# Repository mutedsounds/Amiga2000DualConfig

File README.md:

# Amiga2000DualConfig
Amiga 2000 Coprocessor Board to support 2 selectable CPUs, 2 selectable kickstart ROMs (+ 2x A/B configuration options) at boot or reset.

The **DualConfig** project was born out of an observation: some programs, games or demos don't work with all 680x0 processor models or all kickstart versions.

This project allows you to run the Amiga 2000 in legacy mode (68000 & Kickstart1.3) or with the legacy CPU and a more recent kickstart (68000 & Kickstart 3.x) or with a TerribleFire-type card (68030 & Kickstart3.x) for instance. It also provides two additional controls, one can be used to control a DF0 selector for instance. 

There is no need to power-off the Amiga to change the configuration. It can be changed anytime while the Amiga is powered-on. It will be taken in account on the next reset. Each of the 4 configuration parameters (CPU, Kickstart, param3, param4) can be selected using a latched SPST Off-On switch, with optional illumination.

The solution consists of two PCBs:

1. A "DualCpuAdapter" card that fits into the coprocessor slot. It is inspired by the [Open Amiga 2000 Copro Adapter](https://github.com/SukkoPera/OpenAmiga2000CoproAdapter) project. It allows:

   a) permanent installation of two CPUs in the Amiga with selection of one of the two installed CPUs via a SPST latched Off-On switch;

   b) selection of one of two Kickstarts via a SPST latch Off-On switch;

   c) optionally two other configuration parameters, each controlled via a latchsed SPST Off-On switch, one can be used to drive a ["DF0 Selector" board with a SPST control interface such as the one developped by Jussi Kilpelainen](https://jussikilpelainen.kapsi.fi/wordpress/?p=256)

   d) a led illumination driver for each parameter, enabling the use of illuminated switches 

2. A "DualKickAdapter" card that fits in the Kickstart DIP40 slot, allowing a permanent installation of two kickstart ROMs in the Amiga. Kickstart selection can be controlled either by the "DualCpuAdapter" card or by a DPDT On-On switch. 

The "DualKickAdapter" can be controlled by the "DualCpuAdapter" board by connecting 2 wires from the KICK1_CSn & KICK2_CSn header pins of the "DualCpuAdapter" board to the middle pins of the 2x3 header "SW DPDT", CSn_A & CSn_B.

The [CIT Relay GH Series](http://citrelay.com/view_switch.php?series=GH) are illuminated SPST latching off-on pushbutton switches with a small enough diameter of 10mm to be installed on the lower area of the bottom chassis of the Amiga 2000.

I made this project initially for personal use. It is operational and free of license. 

|:warning:**IMPORTANT: The KiCad files provided in the github repository have been translated from another commercial PCB design tool. The latest beta version (7.99) is required to open the files. I strongly advise to double check the KiCad PCB design files before sending to production. Please feel free to propose document updates.** |
|-----------------------------------------|

DualCpuAdapter, CPU1 side  | DualCpuAdapter, CPU2 side | DualKickAdapter
:-------------------------:|:-------------------------:|:-------------------------:
|  |  |  |

:camera:
|-----------------------------------------|

Legacy configuration 68000 (switch off) with Kickstart 1.3 (switch off) | Legacy CPU 68000 (switch off) with Kickstart 3.2.2 (switch on) | TF536 accelerator (switch on) with Kickstart 3.2.2 (switch on)
:-------------------------:|:-------------------------:|:-------------------------:
|  |  |  |

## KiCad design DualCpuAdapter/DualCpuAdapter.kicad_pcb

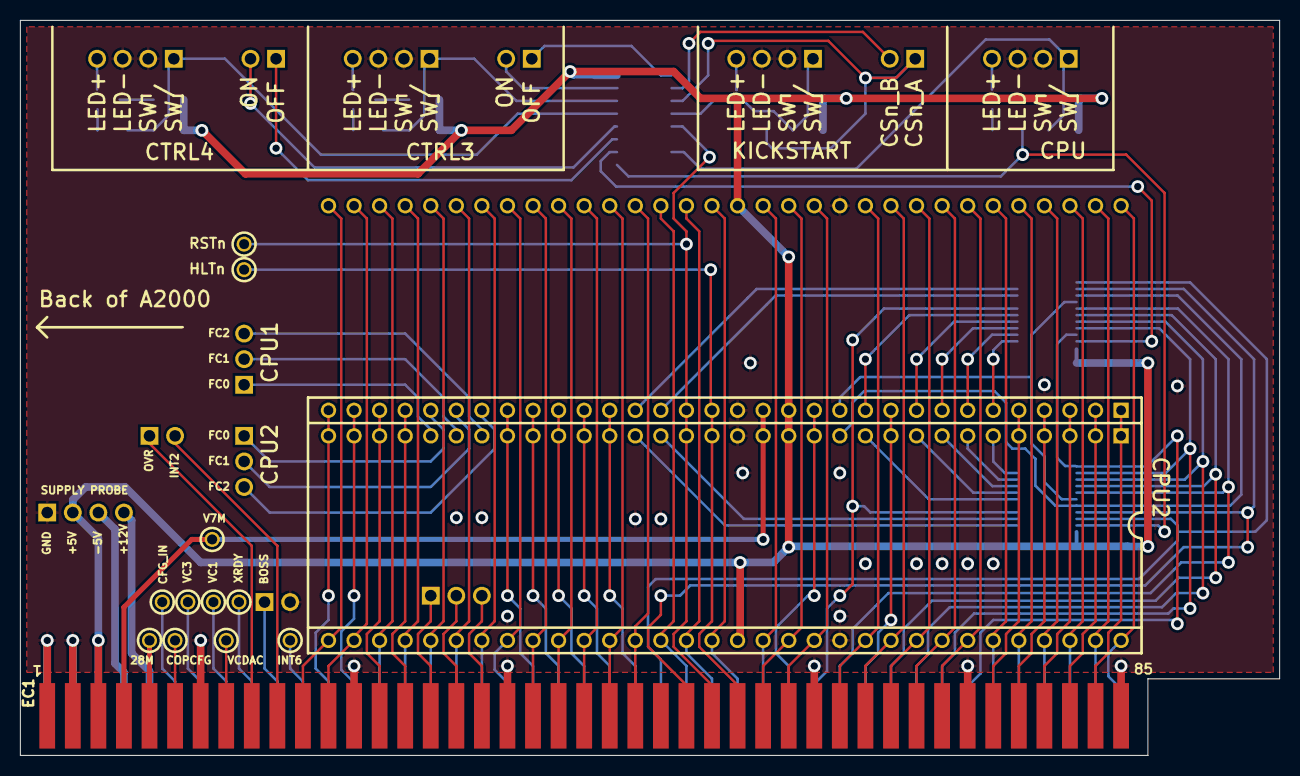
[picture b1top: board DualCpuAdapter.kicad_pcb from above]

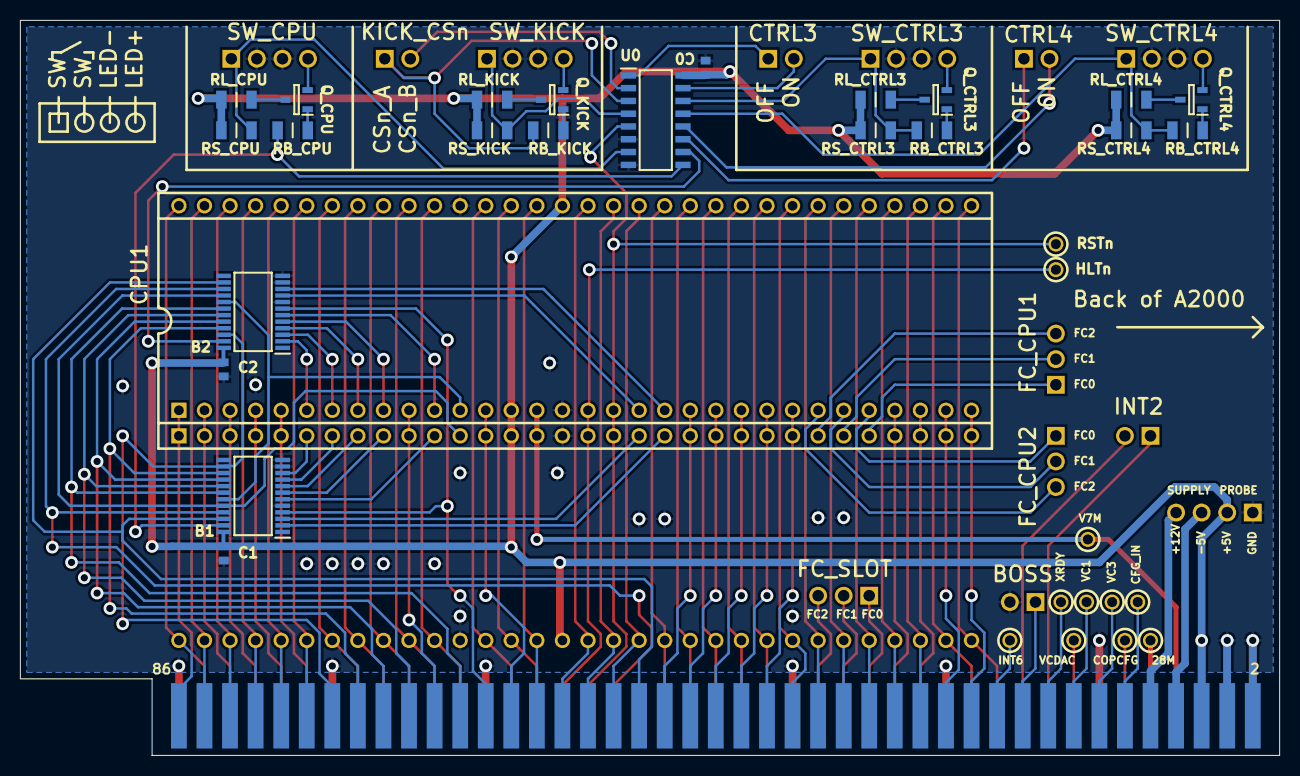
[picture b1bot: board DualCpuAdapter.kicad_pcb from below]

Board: 2 copper layers, 125.1 x 73.0 mm, 49 parts (47 on the bottom side), 111 nets.

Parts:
28M: Test Point; Test Point Throughhole 60mil
B1, B2: SN74CBTD3861PWR; SOP65P640X120-24N
BOSS: Header 1x2 SSS; Harwin M20-9770246
C0, C1, C2: X7R; SMD 1608 X95N
CFG_IN: Test Point; Test Point Throughhole 60mil
COPCFG: Test Point; Test Point Throughhole 60mil
CPU1, CPU2: MC68000P; DIP64 900mil 2xSIP32
CTRL3, CTRL4: Header 1x2 SSS; Molex 705530001
EC1: Card Edge 86pos; Card Edge 86DS 100mil
FC_CPU1, FC_CPU2: Header 1x3 SSS; Harwin M20-9770346
FC_SLOT: Header 1x3 SSS; Harwin M20-9770346
HLTn: Test Point; Test Point Throughhole 60mil
INT2: Header 1x2 SSS; Harwin M20-9770246
INT6: Test Point; Test Point Throughhole 60mil
KICK_CSn: Header 1x2 SSS; Molex 705530001
Q_CPU: PMBT2222A_235; SOT95P230X110-3N
Q_CTRL3, Q_CTRL4: PMBT2222A_235; SOT95P230X110-3N
Q_KICK: PMBT2222A_235; SOT95P230X110-3N
RB_CPU: %; SMD C3216 X 60N
RB_CTRL3, RB_CTRL4: %; SMD C3216 X 60N
RB_KICK: %; SMD C3216 X 60N
RL_CPU: %; SMD C3216 X 60N
RL_CTRL3, RL_CTRL4: %; SMD C3216 X 60N
RL_KICK: %; SMD C3216 X 60N
RSTn: Test Point; Test Point Throughhole 60mil
RS_CPU: %; SMD C3216 X 60N
RS_CTRL3, RS_CTRL4: %; SMD C3216 X 60N
RS_KICK: %; SMD C3216 X 60N
SUPPLY: Header 1x4 SSS; Harwin M20-9770446
SW_CPU: Header 1x4 SSS; Molex 705530003
SW_CTRL3, SW_CTRL4: Header 1x4 SSS; Molex 705530003
SW_KICK: Header 1x4 SSS; Molex 705530003
U0: CD4042BDR; SOIC127P600X175-16N
V7M: Test Point; Test Point Throughhole 60mil
VC1, VC3: Test Point; Test Point Throughhole 60mil
VCDAC: Test Point; Test Point Throughhole 60mil
XRDY: Test Point; Test Point Throughhole 60mil

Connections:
+5V: B1.24 (VCC), B2.24 (VCC), C0.1, C1.1, C2.1, CPU1.14 (VCC), CPU1.49 (VCC), CPU2.14 (VCC), CPU2.49 (VCC), EC1.5, EC1.6, RL_CPU.1, RL_CTRL3.1, RL_CTRL4.1, RL_KICK.1, RS_CPU.2, RS_CTRL3.2, RS_CTRL4.2, RS_KICK.2, SUPPLY.2, U0.16 (VDD)
+12V: EC1.10, SUPPLY.4
-5V: EC1.8, SUPPLY.3
/A1: CPU1.29 (A1), CPU2.29 (A1), EC1.29
/A2: CPU1.30 (A2), CPU2.30 (A2), EC1.27
/A3: CPU1.31 (A3), CPU2.31 (A3), EC1.26
/A4: CPU1.32 (A4), CPU2.32 (A4), EC1.24
/A5: CPU1.33 (A5), CPU2.33 (A5), EC1.21
/A6: CPU1.34 (A6), CPU2.34 (A6), EC1.23
/A7: CPU1.35 (A7), CPU2.35 (A7), EC1.28
/A8: CPU1.36 (A8), CPU2.36 (A8), EC1.30
/A9: CPU1.37 (A9), CPU2.37 (A9), EC1.32
/A10: CPU1.38 (A10), CPU2.38 (A10), EC1.34
/A11: CPU1.39 (A11), CPU2.39 (A11), EC1.36
/A12: CPU1.40 (A12), CPU2.40 (A12), EC1.38
/A13: CPU1.41 (A13), CPU2.41 (A13), EC1.39
/A14: CPU1.42 (A14), CPU2.42 (A14), EC1.41
/A15: CPU1.43 (A15), CPU2.43 (A15), EC1.43
/A16: CPU1.44 (A16), CPU2.44 (A16), EC1.45
/A17: CPU1.45 (A17), CPU2.45 (A17), EC1.47
/A18: CPU1.46 (A18), CPU2.46 (A18), EC1.52
/A19: CPU1.47 (A19), CPU2.47 (A19), EC1.54
/A20: CPU1.48 (A20), CPU2.48 (A20), EC1.56
/A21: CPU1.50 (A21), CPU2.50 (A21), EC1.58
/A22: CPU1.51 (A22), CPU2.51 (A22), EC1.57
/A23: CPU1.52 (A23), CPU2.52 (A23), EC1.59
/ASn_CPU1: B1.10 (A9), CPU1.6 (~AS)
/ASn_CPU2: B2.2 (A1), CPU2.6 (~AS)
/ASn_SLOT: B1.14 (B9), B2.22 (B1), EC1.74
/BERRn: CPU1.22 (~BERR), CPU2.22 (~BERR), EC1.46
/BGACKn_CPU1: B1.20 (B3), B2.16 (B7), CPU1.12 (~BGACK)
/BGACKn_CPU2: B1.19 (B4), B2.17 (B6), CPU2.12 (~BGACK)
/BGACKn_SLOT: B1.4 (A3), B2.7 (A6), EC1.62
/BGn_CPU1: B1.6 (A5), CPU1.11 (~BG)
/BGn_CPU2: B2.6 (A5), CPU2.11 (~BG)
/BGn_SLOT: B1.18 (B5), B2.18 (B5), EC1.64
/BRn: CPU1.13 (~BR), CPU2.13 (~BR), EC1.60
/CPU1_SELn: B1.23 (~OE), U0.9 (~Q2)
/CPU2_SELn: B2.23 (~OE), U0.10 (Q2)
/CTRL3_OFF: CTRL3.1, U0.1 (Q4)
/CTRL3_ON: CTRL3.2, U0.15 (~Q4)
/CTRL3_SW: RB_CTRL3.1, RS_CTRL3.1, SW_CTRL3.1, U0.14 (D4)
/CTRL4_OFF: CTRL4.1, U0.11 (Q3)
/CTRL4_ON: CTRL4.2, U0.12 (~Q3)
/CTRL4_SW: RB_CTRL4.1, RS_CTRL4.1, SW_CTRL4.1, U0.13 (D3)
/D0: CPU1.5 (D0), CPU2.5 (D0), EC1.75
/D1: CPU1.4 (D1), CPU2.4 (D1), EC1.77
/D2: CPU1.3 (D2), CPU2.3 (D2), EC1.79
/D3: CPU1.2 (D3), CPU2.2 (D3), EC1.81
/D4: CPU1.1 (D4), CPU2.1 (D4), EC1.83
/D5: CPU1.64 (D5), CPU2.64 (D5), EC1.86
/D6: CPU1.63 (D6), CPU2.63 (D6), EC1.84
/D7: CPU1.62 (D7), CPU2.62 (D7), EC1.82
/D8: CPU1.61 (D8), CPU2.61 (D8), EC1.80
/D9: CPU1.60 (D9), CPU2.60 (D9), EC1.78
/D10: CPU1.59 (D10), CPU2.59 (D10), EC1.76
/D11: CPU1.58 (D11), CPU2.58 (D11), EC1.71
/D12: CPU1.57 (D12), CPU2.57 (D12), EC1.69
/D13: CPU1.56 (D13), CPU2.56 (D13), EC1.67
/D14: CPU1.55 (D14), CPU2.55 (D14), EC1.65
/D15: CPU1.54 (D15), CPU2.54 (D15), EC1.63
/DTACKn: CPU1.10 (~DTACK), CPU2.10 (~DTACK), EC1.66
/E_CPU1: B1.2 (A1), CPU1.20 (E)
/E_CPU2: B2.10 (A9), CPU2.20 (E)
/E_SLOT: B1.22 (B1), B2.14 (B9), EC1.50
/FC0_CPU1: CPU1.28 (FC0), FC_CPU1.1
/FC0_CPU2: CPU2.28 (FC0), FC_CPU2.1
/FC1_CPU1: CPU1.27 (FC1), FC_CPU1.2
/FC1_CPU2: CPU2.27 (FC1), FC_CPU2.2
/FC2_CPU1: CPU1.26 (FC2), FC_CPU1.3
/FC2_CPU2: CPU2.26 (FC2), FC_CPU2.3
/HLTn: CPU1.17 (~HALT), CPU2.17 (~HALT), EC1.55
/INT2: EC1.19, INT2.2
/INT6: EC1.22, INT6.1
/IPL0n: CPU1.25 (~IPL0), CPU2.25 (~IPL0), EC1.40
/IPL1n: CPU1.24 (~IPL1), CPU2.24 (~IPL1), EC1.42
/IPL2n: CPU1.23 (~IPL2), CPU2.23 (~IPL2), EC1.44
/LDSn_CPU1: B1.8 (A7), CPU1.8 (~LDS)
/LDSn_CPU2: B2.4 (A3), CPU2.8 (~LDS)
/LDSn_SLOT: B1.16 (B7), B2.20 (B3), EC1.70
/OVR: EC1.17, INT2.1
/RSTn: CPU1.18 (~RST), CPU2.18 (~RST), EC1.53, U0.5 (CLOCK)
/RWn_CPU1: B1.7 (A6), CPU1.9 (R/~W)
/RWn_CPU2: B2.5 (A4), CPU2.9 (R/~W)
/RWn_SLOT: B1.17 (B6), B2.19 (B4), EC1.68
/UDSn_CPU1: B1.9 (A8), CPU1.7 (~UDS)
/UDSn_CPU2: B2.3 (A2), CPU2.7 (~UDS)
/UDSn_SLOT: B1.15 (B8), B2.21 (B2), EC1.72
/V7M: CPU1.15 (CLK), CPU2.15 (CLK), EC1.7
/VC1: EC1.16, VC1.1
/VC3: EC1.14, VC3.1
/VMAn_CPU1: B1.3 (A2), CPU1.19 (~VMA)
/VMAn_CPU2: B2.9 (A8), CPU2.19 (~VMA)
/VMAn_SLOT: B1.21 (B2), B2.15 (B8), EC1.51
/VPAn: CPU1.21 (~VPA), CPU2.21 (~VPA), EC1.48
CPU_LED: Q_CPU.2, SW_CPU.4
CPU_SW: RS_CPU.1, SW_CPU.1
GND: B1.5 (A4), B1.11 (A10), B1.12 (GND), B2.8 (A7), B2.11 (A10), B2.12 (GND), BOSS.2, C0.2, C1.2, C2.2, CPU1.16 (GND), CPU1.53 (GND), CPU2.16 (GND), CPU2.53 (GND), EC1.1, EC1.2, EC1.3, EC1.4, EC1.13, EC1.25, EC1.37, EC1.49, EC1.61, EC1.73, EC1.85, SUPPLY.1, SW_CPU.2, SW_CPU.3, SW_CTRL3.2, SW_CTRL3.3, SW_CTRL4.2, SW_CTRL4.3, SW_KICK.2, SW_KICK.3, U0.6 (POLARITY), U0.8 (VSS)
KICK1_CSN: KICK_CSn.1, RB_KICK.1
KICK_SW: RS_KICK.1, SW_KICK.1
unnamed: Q_CTRL3.1 (B), RB_CTRL3.2
unnamed: Q_CTRL3.3 (C), RL_CTRL3.2
unnamed: Q_CTRL3.2 (E), SW_CTRL3.4
unnamed: Q_CTRL4.1 (B), RB_CTRL4.2
unnamed: Q_CTRL4.3 (C), RL_CTRL4.2
unnamed: Q_CTRL4.2 (E), SW_CTRL4.4
NetQ_CPU_1: Q_CPU.1, RB_CPU.2
NetQ_CPU_3: Q_CPU.3, RL_CPU.2
NetQ_KICK_1: Q_KICK.1, RB_KICK.2
NetQ_KICK_2: Q_KICK.2, SW_KICK.4
NetQ_KICK_3: Q_KICK.3, RL_KICK.2

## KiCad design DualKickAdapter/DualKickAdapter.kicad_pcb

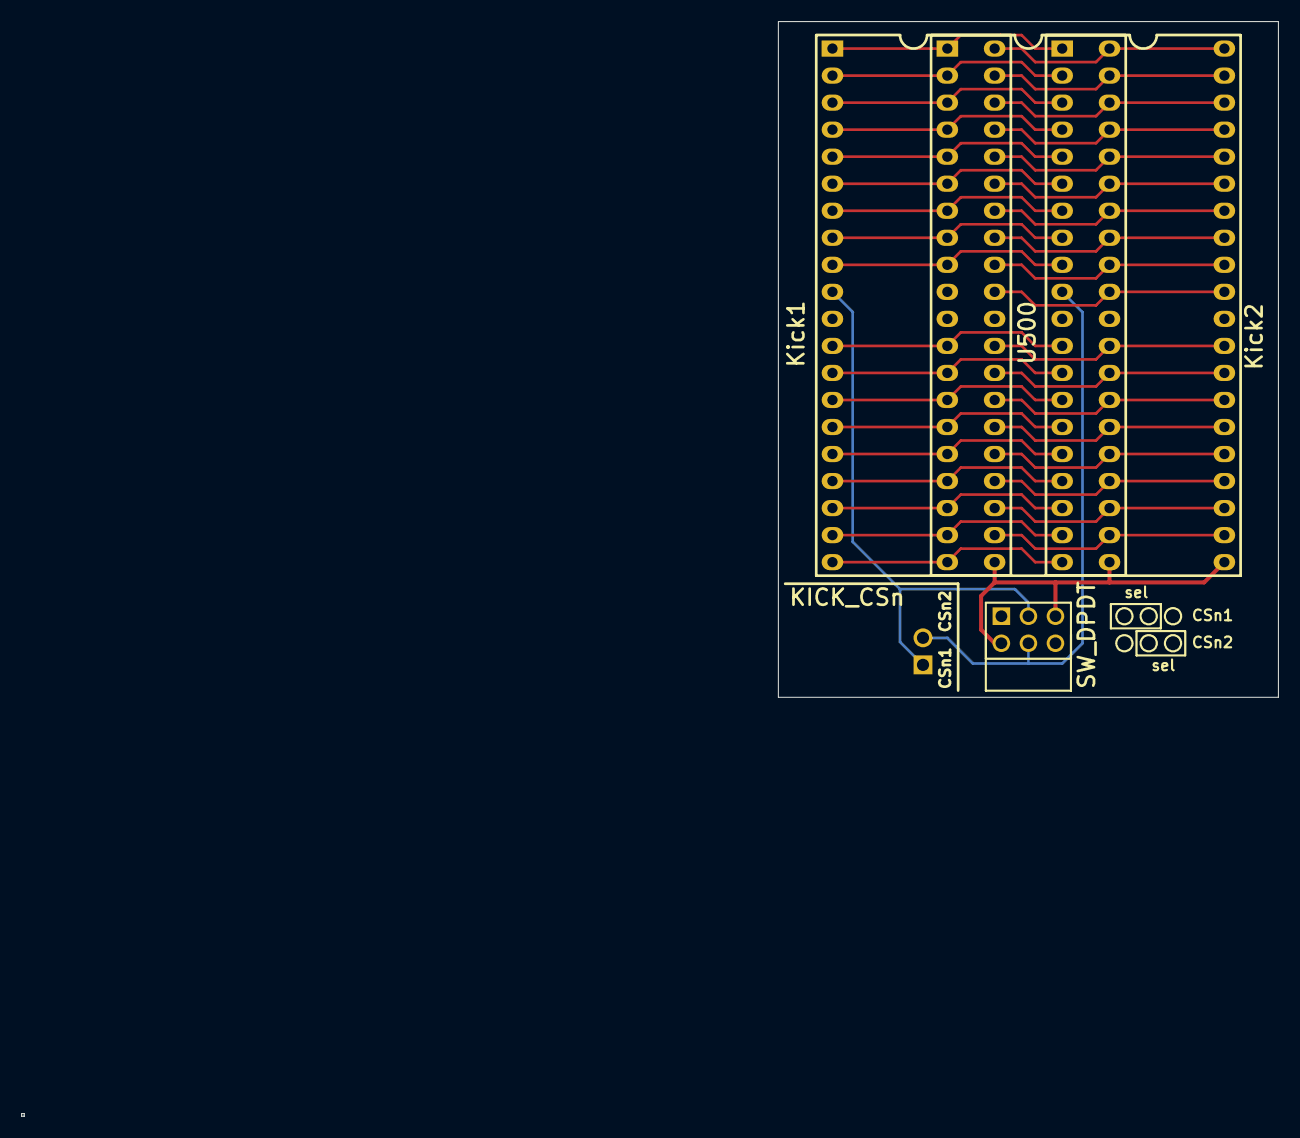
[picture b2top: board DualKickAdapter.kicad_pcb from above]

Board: 2 copper layers, 47.0 x 63.5 mm, 5 parts (0 on the bottom side), 40 nets.

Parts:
KICK_CSn: Header 1x2 DSS; Molex 705530001
Kick1, Kick2: DIP40 2x20 600mil; DIP40 600mil 2xSIP20 oval
SW_DPDT: Header 2x3 DSS; Amphenol 10129382-906002BLF alt
U500: DIP40 2x20 600mil; DIP40 600mil 2xSIP20 spacer oval

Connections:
A0: Kick1.9, Kick2.9, U500.9
A1: Kick1.8, Kick2.8, U500.8
A2: Kick1.7, Kick2.7, U500.7
A3: Kick1.6, Kick2.6, U500.6
A4: Kick1.5, Kick2.5, U500.5
A5: Kick1.4, Kick2.4, U500.4
A6: Kick1.3, Kick2.3, U500.3
A7: Kick1.2, Kick2.2, U500.2
A8: Kick1.40, Kick2.40, U500.40
A9: Kick1.39, Kick2.39, U500.39
A10: Kick1.38, Kick2.38, U500.38
A11: Kick1.37, Kick2.37, U500.37
A12: Kick1.36, Kick2.36, U500.36
A13: Kick1.35, Kick2.35, U500.35
A14: Kick1.34, Kick2.34, U500.34
A15: Kick1.33, Kick2.33, U500.33
A16: Kick1.32, Kick2.32, U500.32
A17: Kick1.31, Kick2.31, U500.31
CSN_A: KICK_CSn.1, SW_DPDT.3
CSN_B: KICK_CSn.2, SW_DPDT.4
D0: Kick1.13, Kick2.13, U500.13
D1: Kick1.15, Kick2.15, U500.15
D2: Kick1.17, Kick2.17, U500.17
D3: Kick1.19, Kick2.19, U500.19
D4: Kick1.22, Kick2.22, U500.22
D5: Kick1.24, Kick2.24, U500.24
D6: Kick1.26, Kick2.26, U500.26
D7: Kick1.28, Kick2.28, U500.28
D8: Kick1.14, Kick2.14, U500.14
D9: Kick1.16, Kick2.16, U500.16
D10: Kick1.18, Kick2.18, U500.18
D11: Kick1.20, Kick2.20, U500.20
D12: Kick1.23, Kick2.23, U500.23
D13: Kick1.25, Kick2.25, U500.25
D14: Kick1.27, Kick2.27, U500.27
D15: Kick1.29, Kick2.29, U500.29
GND: Kick1.11, Kick1.30, Kick2.11, Kick2.30, SW_DPDT.1, SW_DPDT.6, U500.11, U500.30
NC: Kick1.1, Kick2.1, U500.1
OEn: Kick1.12, Kick2.12, U500.12
VCC: Kick1.21, Kick2.21, SW_DPDT.2, SW_DPDT.5, U500.21

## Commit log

2023-12-06 README.md: initial version
2023-12-06 Kicad files for CpuSelector Board and KickstartSelector board added
2023-12-06 README.md: added minor precision in warning note
2023-12-07 BOM added
    TO BE VERIFIED: does the proposed Molex connector 705530001 fit in the mid 2-pin of the SW_DPDT footprint of the DualKick board?
2023-12-07 Restructuring: each board has its own folder; Added: snapshots of boards and amiga case
2023-12-07 Photos moved to separate folder
2023-12-08 Update README.md: added required Kicad version 7.99 (8 beta)
2023-12-08 Update README.md: PCB board snapshots added
2023-12-08 [Photos] PCB snapshots reframed
2023-12-08 Update README.md: A2000 configuration photos on same row
